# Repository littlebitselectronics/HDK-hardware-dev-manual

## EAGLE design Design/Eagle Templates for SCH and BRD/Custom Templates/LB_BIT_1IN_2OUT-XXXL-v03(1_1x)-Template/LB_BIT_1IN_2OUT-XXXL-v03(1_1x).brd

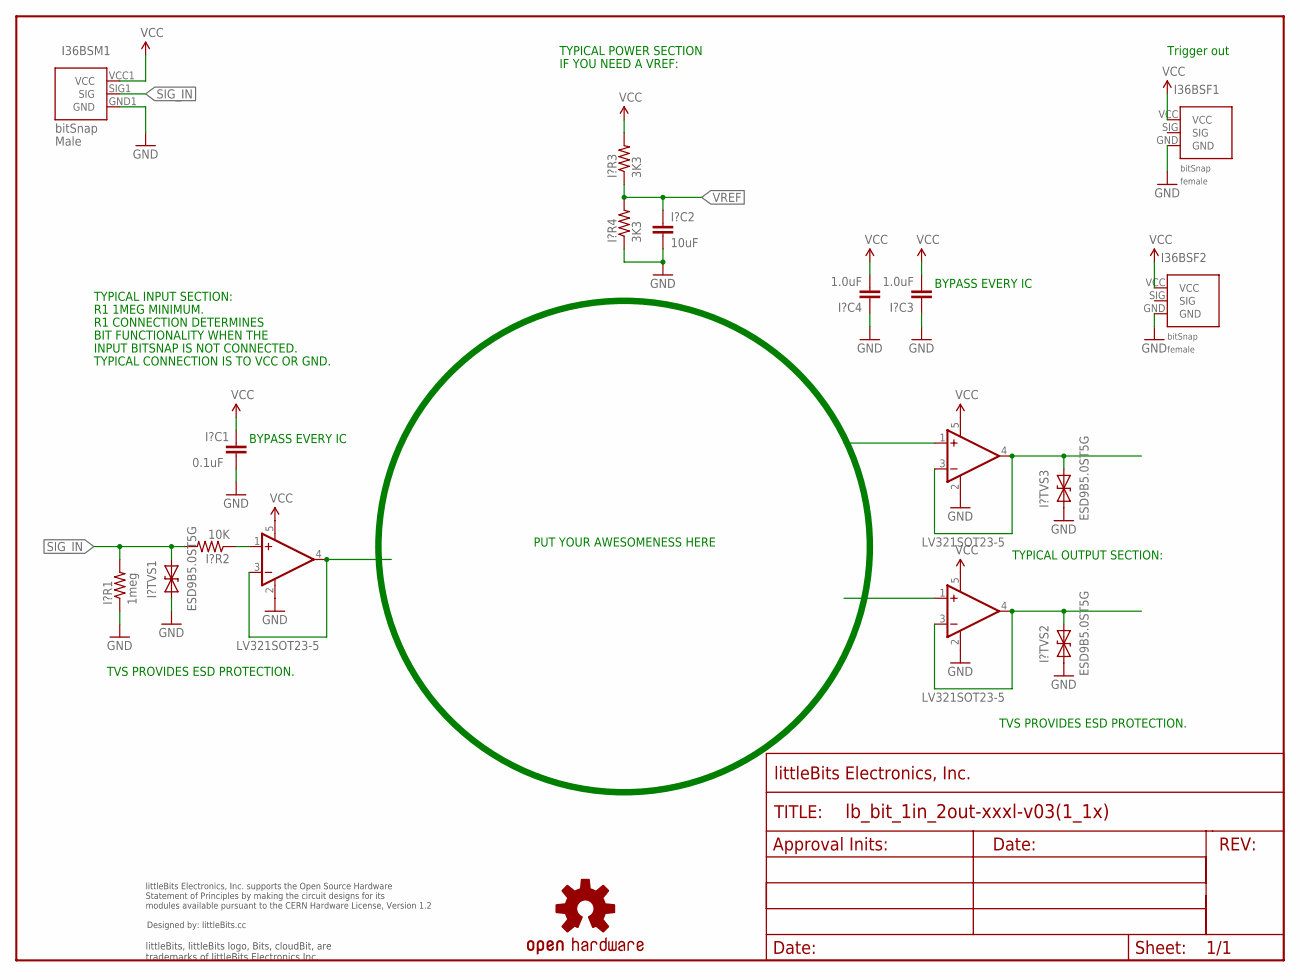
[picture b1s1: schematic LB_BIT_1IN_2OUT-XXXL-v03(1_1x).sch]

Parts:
FRAME1: FRAME-LETTER; FABDWG01-OHW
I36BSF1, I36BSF2: BITSNAP_V03_FEMALE
I36BSM1: BITSNAP_V03_MALE
I?C1: 0.1uF; CAP-0603
I?C2: 10uF; CAP-0603
I?C3, I?C4: 1.0uF; CAP-0603
I?R1: 1meg; RES-0603
I?R2: 10K; RES-0603
I?R3, I?R4: 3K3; RES-0603
I?TVS1, I?TVS2, I?TVS3: ESD9B5.0ST5G; SOD-923
U1, U2, U3: LV321SOT23-5; SOT23-5
U$1: OSHW-LOGOL; OSHW-LOGO-L
U$3: OSHWCREDIT

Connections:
GND: I36BSF1.GND, I36BSF2.GND, I36BSM1.GND1 (GND), I?C1.2, I?C2.2, I?C3.1, I?C4.1, I?R1.1, I?R4.1, I?TVS1.1 (A), I?TVS2.1 (A), I?TVS3.1 (A), U1.2 (V-), U2.2 (V-), U3.2 (V-)
unnamed: U1.3 (-IN), U1.4 (OUT)
unnamed: I?R2.1, U1.1 (+IN)
SIG_IN: I36BSM1.SIG1 (SIG), I?R1.2, I?R2.2, I?TVS1.2 (C)
SIG_OUT: I?TVS2.2 (C), U2.3 (-IN), U2.4 (OUT)
SIG_OUT1: I?TVS3.2 (C), U3.3 (-IN), U3.4 (OUT)
VCC: I36BSF1.VCC, I36BSF2.VCC, I36BSM1.VCC1 (VCC), I?C1.1, I?C3.2, I?C4.2, I?R3.2, U1.5 (V+), U2.5 (V+), U3.5 (V+)
VREF: I?C2.1, I?R3.1, I?R4.2

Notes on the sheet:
Trigger out
R1 1MEG MINIMUM.
R1 CONNECTION DETERMINES
BIT FUNCTIONALITY WHEN THE
INPUT BITSNAP IS NOT CONNECTED.
TYPICAL CONNECTION IS TO VCC OR GND.
TVS PROVIDES ESD PROTECTION.
TYPICAL INPUT SECTION:
TYPICAL POWER SECTION
IF YOU NEED A VREF:
PUT YOUR AWESOMENESS HERE
BYPASS EVERY IC
TYPICAL OUTPUT SECTION:

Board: 2 copper layers, 21 parts (14 on the bottom side), 8 nets, no tracks yet.

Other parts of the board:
U$17: OSHW_FILLX150_NOTEXT

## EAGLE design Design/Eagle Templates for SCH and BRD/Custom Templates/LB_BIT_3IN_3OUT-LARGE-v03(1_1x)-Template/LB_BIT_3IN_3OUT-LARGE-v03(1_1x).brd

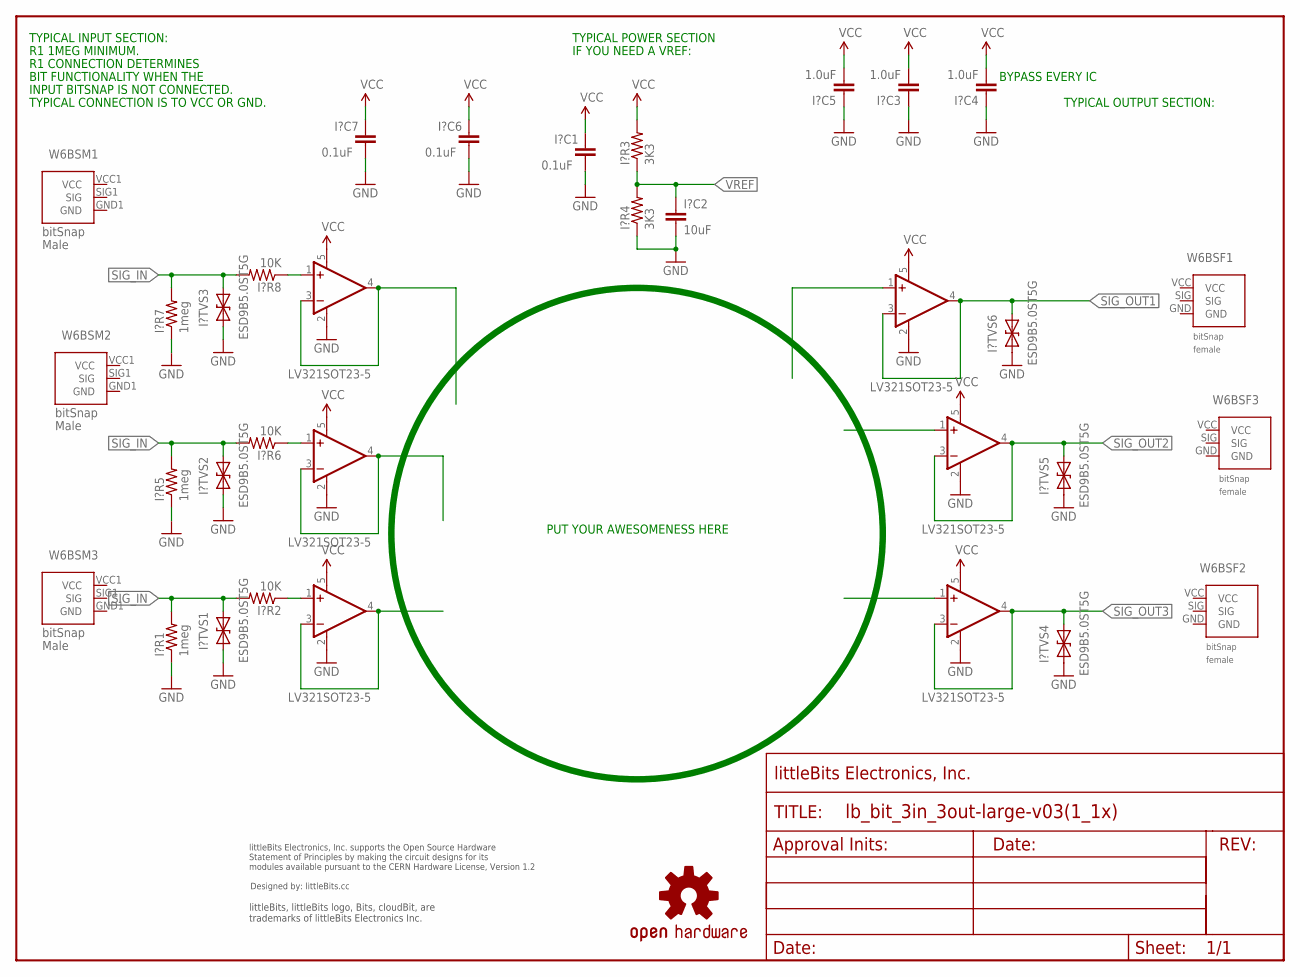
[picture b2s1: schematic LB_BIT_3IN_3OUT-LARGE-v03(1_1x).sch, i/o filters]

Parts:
FRAME1: FRAME-LETTER; FABDWG01-OHW
I?C1, I?C6, I?C7: 0.1uF; CAP-0603
I?C2: 10uF; CAP-0603
I?C3, I?C4, I?C5: 1.0uF; CAP-0603
I?R1, I?R5, I?R7: 1meg; RES-0603
I?R2, I?R6, I?R8: 10K; RES-0603
I?R3, I?R4: 3K3; RES-0603
I?TVS1, I?TVS2, I?TVS3, I?TVS4, I?TVS5, I?TVS6: ESD9B5.0ST5G; SOD-923
U1, U2, U3, U4, U5, U6: LV321SOT23-5; SOT23-5
U$1: OSHWCREDIT
U$70: OSHW-LOGOL; OSHW-LOGO-L
W6BSF1, W6BSF2, W6BSF3: BITSNAP_V03_FEMALE
W6BSM1, W6BSM2, W6BSM3: BITSNAP_V03_MALE

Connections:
GND: I?C1.2, I?C2.2, I?C3.1, I?C4.1, I?C5.1, I?C6.2, I?C7.2, I?R1.1, I?R4.1, I?R5.1, I?R7.1, I?TVS1.1 (A), I?TVS2.1 (A), I?TVS3.1 (A), I?TVS4.1 (A), I?TVS5.1 (A), I?TVS6.1 (A), U1.2 (V-), U2.2 (V-), U3.2 (V-), U4.2 (V-), U5.2 (V-), U6.2 (V-)
unnamed: I?R2.1, U1.1 (+IN)
unnamed: U1.3 (-IN), U1.4 (OUT)
unnamed: U2.3 (-IN), U2.4 (OUT)
unnamed: I?R6.1, U2.1 (+IN)
unnamed: U3.3 (-IN), U3.4 (OUT)
unnamed: I?R8.1, U3.1 (+IN)
SIG_IN: I?R1.2, I?R2.2, I?R5.2, I?R6.2, I?R7.2, I?R8.2, I?TVS1.2 (C), I?TVS2.2 (C), I?TVS3.2 (C)
SIG_OUT1: I?TVS6.2 (C), U6.3 (-IN), U6.4 (OUT)
SIG_OUT2: I?TVS5.2 (C), U5.3 (-IN), U5.4 (OUT)
SIG_OUT3: I?TVS4.2 (C), U4.3 (-IN), U4.4 (OUT)
VCC: I?C1.1, I?C3.2, I?C4.2, I?C5.2, I?C6.1, I?C7.1, I?R3.2, U1.5 (V+), U2.5 (V+), U3.5 (V+), U4.5 (V+), U5.5 (V+), U6.5 (V+)
VREF: I?C2.1, I?R3.1, I?R4.2

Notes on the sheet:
R1 1MEG MINIMUM.
R1 CONNECTION DETERMINES
BIT FUNCTIONALITY WHEN THE
INPUT BITSNAP IS NOT CONNECTED.
TYPICAL CONNECTION IS TO VCC OR GND.
TYPICAL INPUT SECTION:
TYPICAL POWER SECTION
IF YOU NEED A VREF:
PUT YOUR AWESOMENESS HERE
TYPICAL OUTPUT SECTION:
BYPASS EVERY IC

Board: 2 copper layers, 37 parts (27 on the bottom side), 13 nets, no tracks yet.

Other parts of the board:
U$5: OSHW_FILLX150_NOTEXT

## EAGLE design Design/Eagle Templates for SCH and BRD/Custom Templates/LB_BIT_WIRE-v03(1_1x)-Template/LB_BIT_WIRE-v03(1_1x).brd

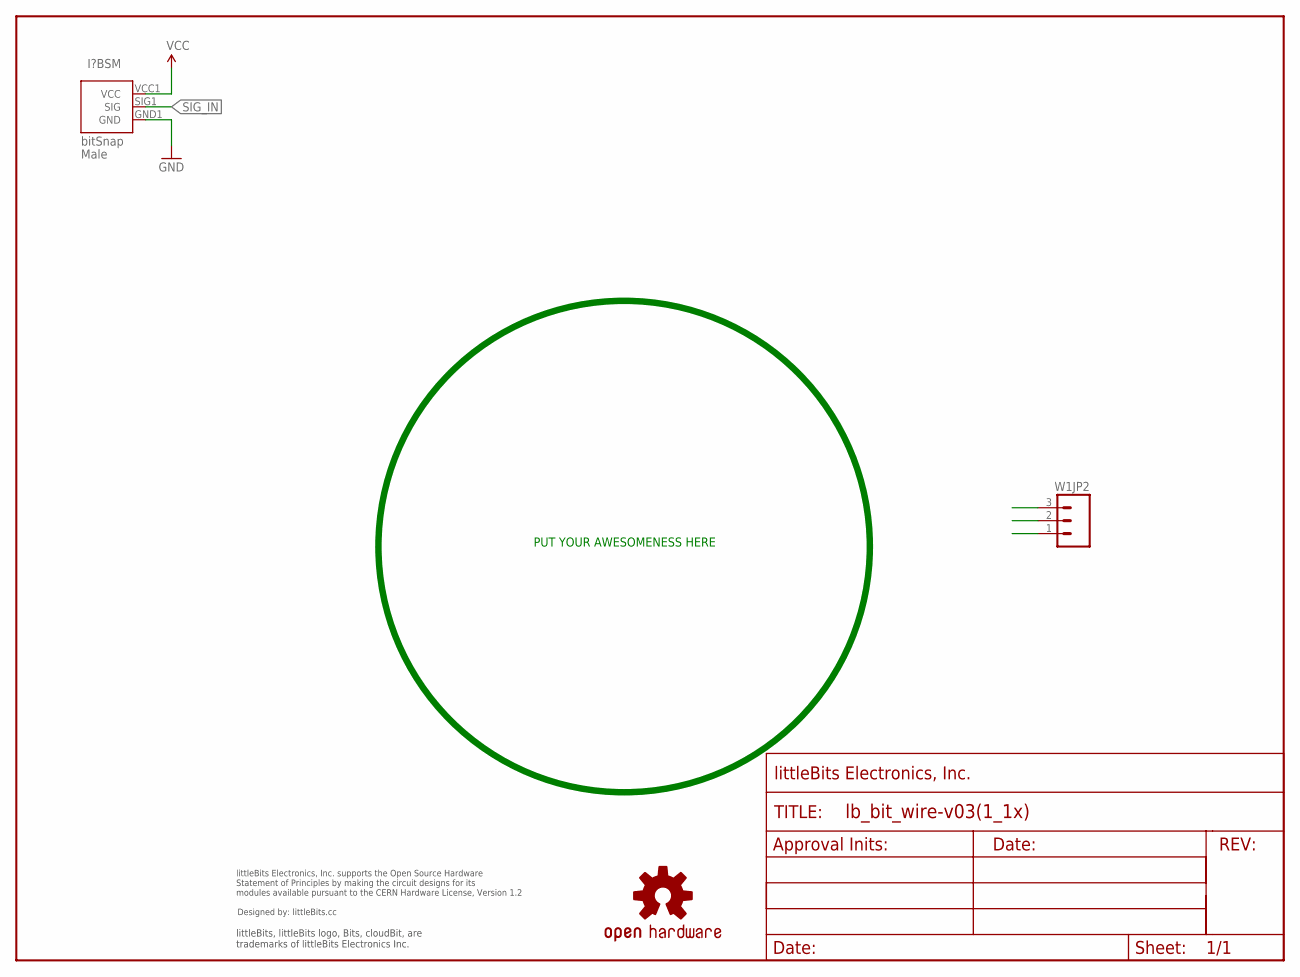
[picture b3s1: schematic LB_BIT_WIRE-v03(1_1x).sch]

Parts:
FRAME1: FRAME-LETTER; FABDWG01-OHW
I?BSM: BITSNAP_V03_MALE
U$2: OSHWCREDIT
U$5: OSHW-LOGOL; OSHW-LOGO-L
W1JP2: M03SMD; 1X03-1MM-RA

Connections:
GND: I?BSM.GND1 (GND), W1JP2.1
SIG: W1JP2.2
SIG_IN: I?BSM.SIG1 (SIG)
VCC: I?BSM.VCC1 (VCC), W1JP2.3

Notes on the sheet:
PUT YOUR AWESOMENESS HERE

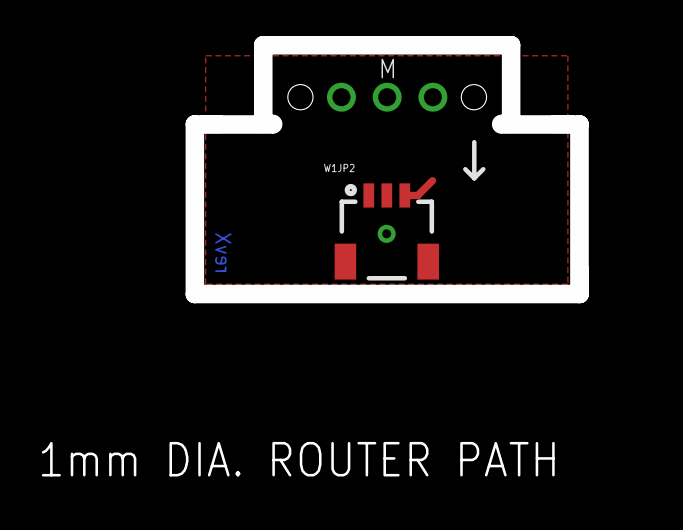
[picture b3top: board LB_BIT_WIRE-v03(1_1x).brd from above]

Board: 2 copper layers, 32.9 x 24.5 mm, 6 parts (0 on the bottom side), 2 nets.

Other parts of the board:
U$4: OSHW_FILLX150_NOTEXT

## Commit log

2014-09-02 Added HDK files
2014-09-03 Removed MFG files and put them in separate Repo
2014-09-08 Templates and libraries moved to another folder.
2014-09-11 Updated HDK with correct file locations, added BOM template
2014-09-15 Added one-sheet, updated library name
2014-09-15 Accepted and stopped tracking changes in design manual
2014-09-16 -Added UI Consideration doc -Updated Welcom Developers doc -Updated logo in PRD template doc -Created PDFs of docs
2014-09-16 Updated doc.
2014-09-16 Changed doc title
2015-02-26 Changed manuals to reflect rtmExample won't be given out until vote threshold is met
2015-04-17 Update HDK materials 17-Apr-2015
2015-04-17 Re-re-update 17-Apr-2015

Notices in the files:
parts and their libraries:
LITTLEBITS: modules available pursuant to the CERN Hardware License,
Version 1.2
LITTLEBITS: modules available pursuant to the CERN Hardware License, Version 1.2
